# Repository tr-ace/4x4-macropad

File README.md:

# 4x4 Macropad

The Macropad is a 16-key keyboard with assignable keys via Python and the KMK library. The microcontroller uses the CircuitPython firmware.

## Usage

Plug the Macropad into your PC with a USB C cable. Windows Explorer may open, since the CircuitPython firmware on the microcontroller may be detected as a mass storage device. You can close Windows Explorer, unless you'd like to customize the keymap.

## Default Keymap

> ℹ️ **Info**
> Row 1, Column 1 is the key closest to the USB C port)

| Row \ Col | Col 1                                | Col 2                           | Col 3                               | Col 4                         |
| --------- | ------------------------------------ | ------------------------------- | ----------------------------------- | ----------------------------- |
| **Row 1** | Ctrl + A<br>(Select All)             | Ctrl + C<br>(Copy)              | Ctrl + V<br>(Paste)                 | Ctrl + S<br>(Save)            |
| **Row 2** | Ctrl + Shift + M<br>(Teams Mute Mic) | Mute Speakers                   | Volume Down                         | Volume Up                     |
| **Row 3** | Win + M<br>(Open Mail)               | Win + E<br>(Open File Explorer) | Ctrl + F<br>(Find)                  | Ctrl + H<br>(Replace)         |
| **Row 4** | Ctrl + Z<br>(Undo)                   | Ctrl + Y<br>(Redo)              | Win + Shift + S <br>(Snipping Tool) | Win + Tab<br>(Switch Windows) |

## Customizing the Keymap

To customize the keymap:

1. Plug in the Macropad via USB C cable
2. Open the CIRCUITPY drive inside of Windows Explorer
3. Open code.py inside of any IDE or Notepad.
4. Scroll down to this section where `keymap` list is defined
5. Change the key values assigned to each key, as needed
6. Save the updated code.py file
7. You might need to unplug, and replug the Macropad back into the PC for the changes to be detected

[See more documentation on KMK for more customization](https://github.com/KMKfw/kmk_firmware/blob/main/docs/en/Getting_Started.md)

## Parts List

- The case is 3D printable comprised of 3 pieces, designed in Fusion 360, and printed on a BambuLabs P1S printer. They are printed in various colors of PLA filament. There are no screws, as everything is press-fit. See [./Code/](./Code/) for the STL files
- The PCB was designed in KiCad, and manufactured by PCBWay.com. See [./KiCad/](./KiCad/) for the KiCad files.
- [Linear MX Switches](https://www.amazon.com/dp/B0D7QW8SQ9?ref=ppx_yo2ov_dt_b_fed_asin_title&th=1)
- [Blank, Rainbow Mixed Keycaps](https://www.amazon.com/dp/B0CQ2WGP2N?ref=ppx_yo2ov_dt_b_fed_asin_title&th=1)
- [1N4148 Diodes](https://www.amazon.com/dp/B00N1ZKU7E?ref=ppx_yo2ov_dt_b_fed_asin_title)
- [Seeed nRF52840 Sense microcontrollers](https://www.amazon.com/dp/B0DJ6PZGB7?ref=ppx_yo2ov_dt_b_fed_asin_title&th=1)

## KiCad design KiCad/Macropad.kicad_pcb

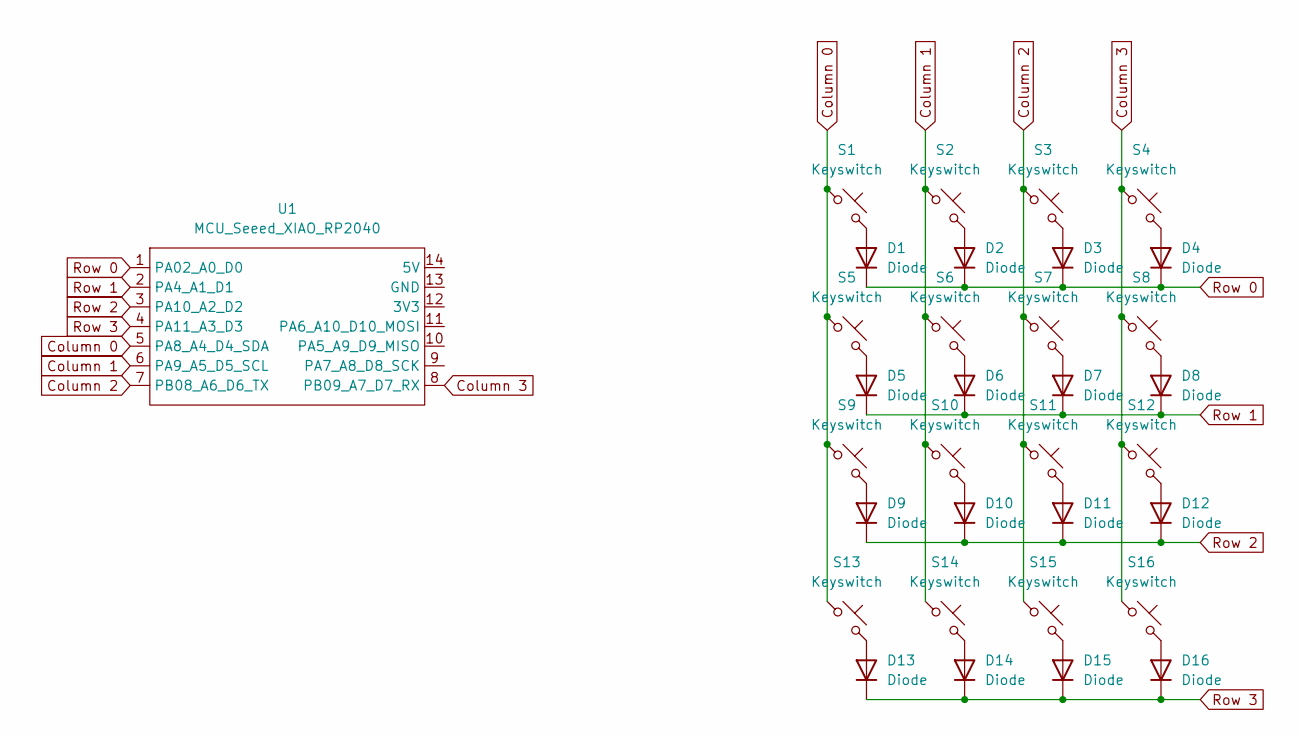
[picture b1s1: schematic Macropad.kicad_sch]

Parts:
D1, D2, D3, D4, D5, D6, D7, D8, D9, D10, D11, D12, D13, D14, D15, D16: Diode; Diode_DO-35
S1, S2, S3, S4, S5, S6, S7, S8, S9, S10, S11, S12, S13, S14, S15, S16: Keyswitch; MX_PCB_1.00u
U1: MCU_Seeed_XIAO_RP2040; Seeed_XIAO_RP2040

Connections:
Column 0: S1.1, S5.1, S9.1, S13.1, U1.5 (PA8_A4_D4_SDA)
Column 1: S2.1, S6.1, S10.1, S14.1, U1.6 (PA9_A5_D5_SCL)
Column 2: S3.1, S7.1, S11.1, S15.1, U1.7 (PB08_A6_D6_TX)
Column 3: S4.1, S8.1, S12.1, S16.1, U1.8 (PB09_A7_D7_RX)
unnamed: D1.2 (A), S1.2
unnamed: D2.2 (A), S2.2
unnamed: D3.2 (A), S3.2
unnamed: D4.2 (A), S4.2
unnamed: D5.2 (A), S5.2
unnamed: D6.2 (A), S6.2
unnamed: D7.2 (A), S7.2
unnamed: D8.2 (A), S8.2
unnamed: D9.2 (A), S9.2
unnamed: D10.2 (A), S10.2
unnamed: D11.2 (A), S11.2
unnamed: D12.2 (A), S12.2
unnamed: D13.2 (A), S13.2
unnamed: D14.2 (A), S14.2
unnamed: D15.2 (A), S15.2
unnamed: D16.2 (A), S16.2
Row 0: D1.1 (K), D2.1 (K), D3.1 (K), D4.1 (K), U1.1 (PA02_A0_D0)
Row 1: D5.1 (K), D6.1 (K), D7.1 (K), D8.1 (K), U1.2 (PA4_A1_D1)
Row 2: D9.1 (K), D10.1 (K), D11.1 (K), D12.1 (K), U1.3 (PA10_A2_D2)
Row 3: D13.1 (K), D14.1 (K), D15.1 (K), D16.1 (K), U1.4 (PA11_A3_D3)

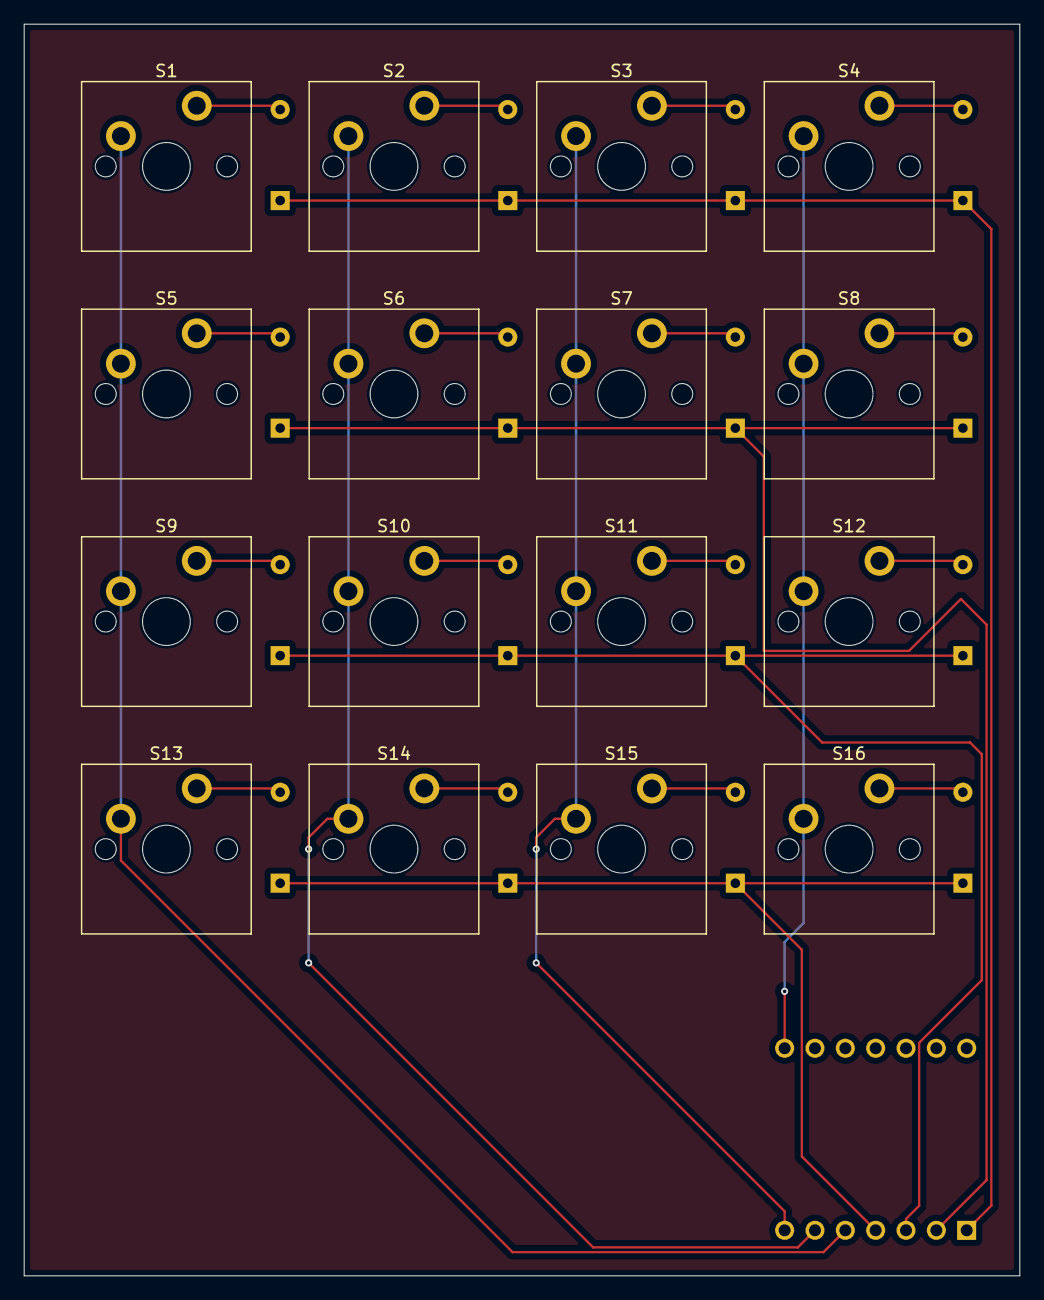
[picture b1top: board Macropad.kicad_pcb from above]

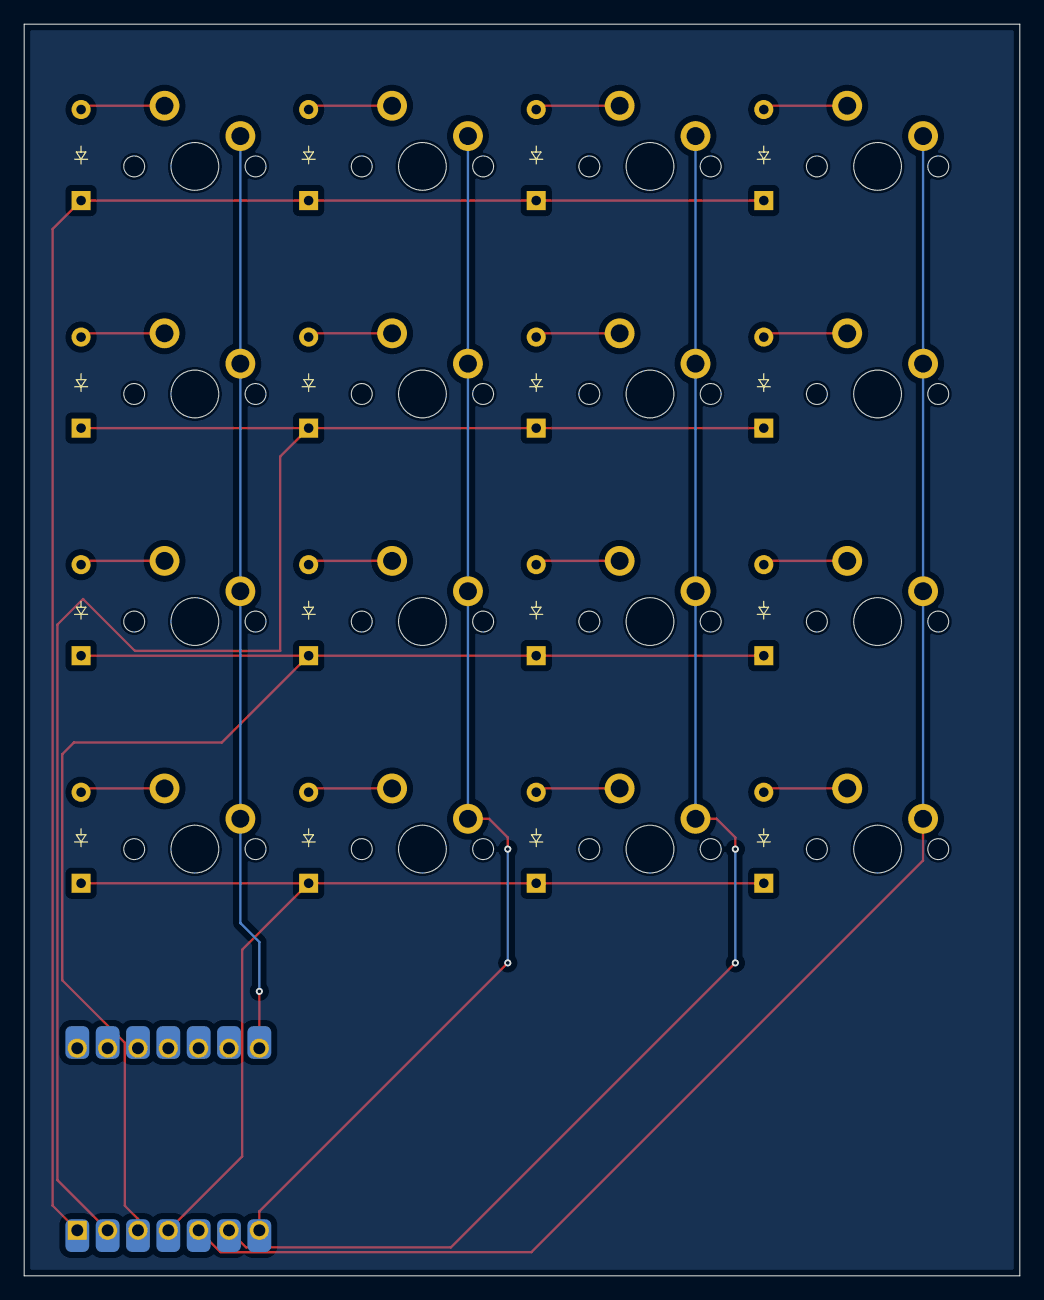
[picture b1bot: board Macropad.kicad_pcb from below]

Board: 2 copper layers, 83.3 x 104.8 mm, 33 parts (17 on the bottom side), 24 nets.

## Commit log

2025-12-18 Add link to github project in source code
2025-12-18 Rename STLs
2025-12-19 Add images
2025-12-20 Fix macro keys and README
